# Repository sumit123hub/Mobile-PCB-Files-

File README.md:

# Custom ESP32 Mobile System PCB

I always dreamed of building my own mobile system. This repo documents my custom ESP32 PCB design featuring a GSM module, display interface, and a complete Battery Management System (BMS).

All subsystems were designed in KiCad and independently validated. Schematics, layout, and testing are complete—I'm just sourcing a suitable display for final integration.

---

## 📷 PCB Images

| Front | Back | 
| :---: | :---: |
|  |  | 

---

| KiCad View |
| :---: |
|  |

---

## ✨ What's on the Board

| Component | Description |
| :--- | :--- |
| **ESP32-WROOM** | Main microcontroller (WiFi + BLE) |
| **GSM Module** | Quectel M65 module |
| **Charging Circuit** | BQ Chip |
| **Display Interface** | SPI for display and I2C for charhing |

---

## 📂 Files

- `Mobile_System.kicad_sch` – Schematic
- `Mobile_System.kicad_pcb` – PCB layout
- `gerbers/` – Manufacturing files
- `BOM.csv` – Bill of Materials

---

## 📌 Status

- ✅ Schematic – Complete
- ✅ PCB Layout – Complete
- ✅ BMS Validation – Passed
- ✅ GSM Validation – Passed
- ⏳ Display Integration – In progress (sourcing)
- ⏳ Firmware – Next step

---

## 🛠️ Tools

- **KiCad** – PCB design
- **Arduino / PlatformIO** – Firmware (coming soon)

---

## 👤 Author

**Sumit Sigdel**  
GitHub: [sumit123hub](https://github.com/sumit123hub)

---

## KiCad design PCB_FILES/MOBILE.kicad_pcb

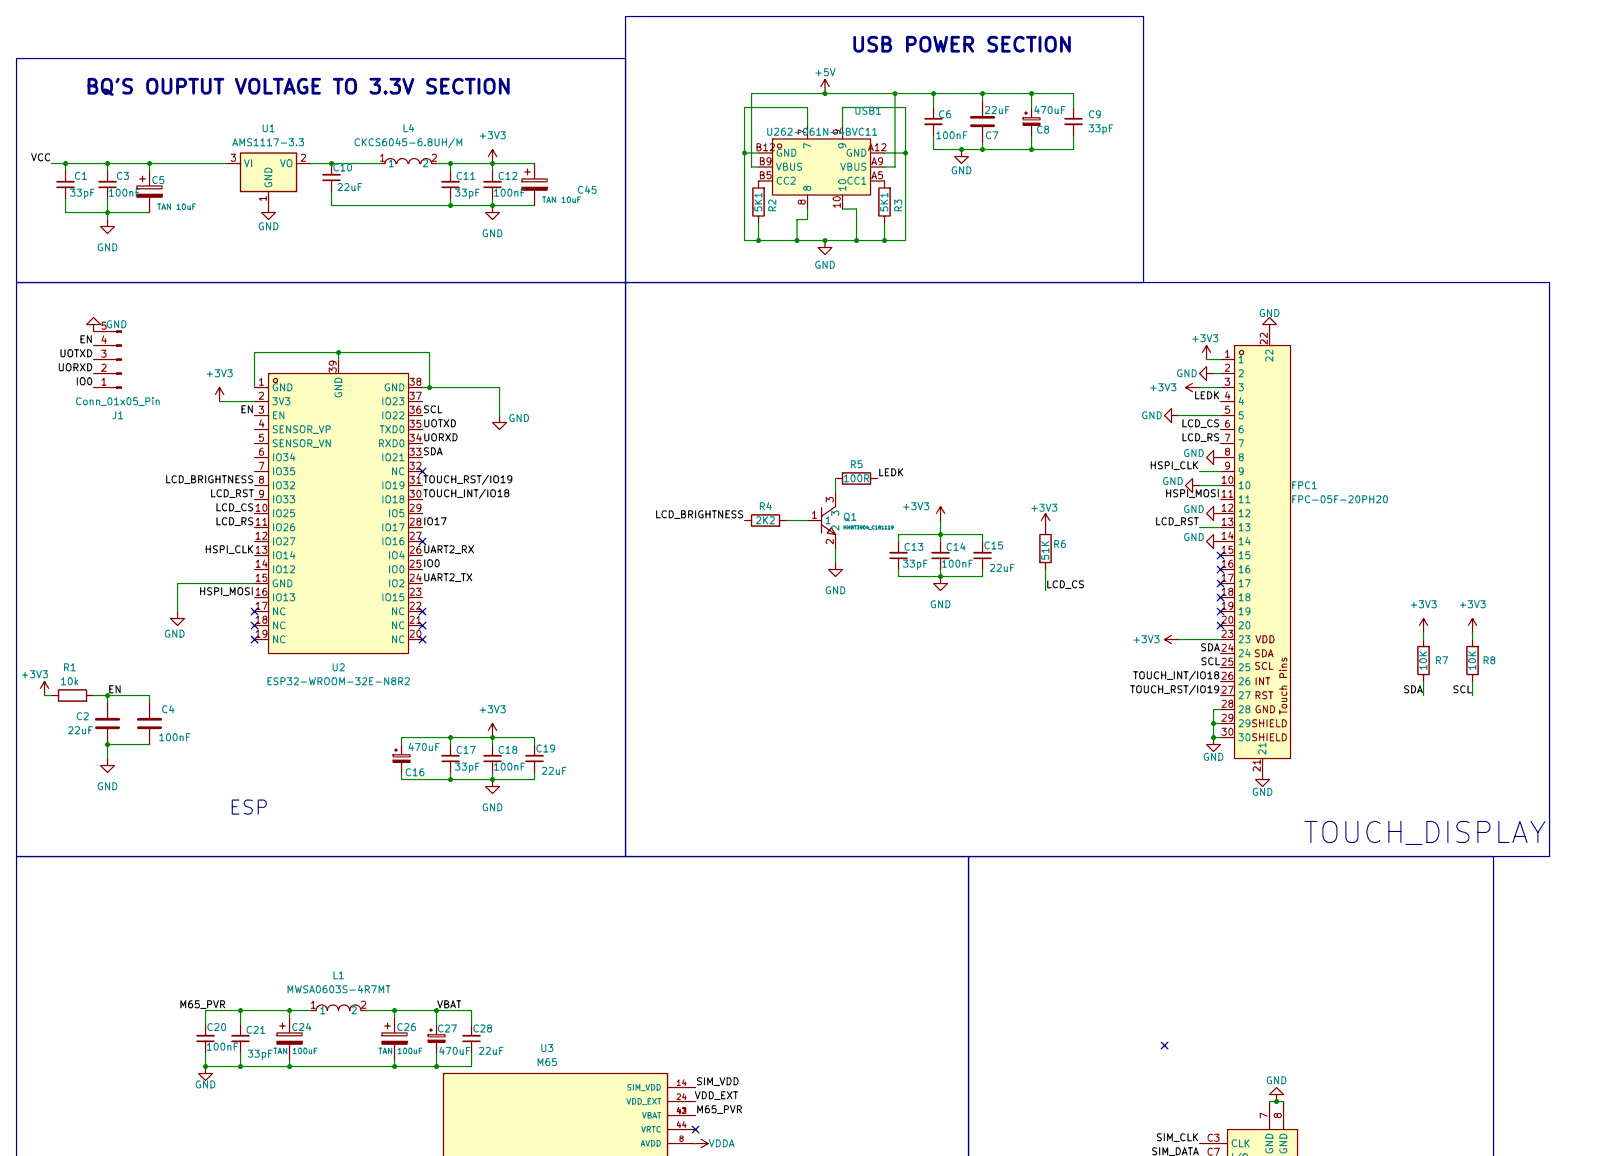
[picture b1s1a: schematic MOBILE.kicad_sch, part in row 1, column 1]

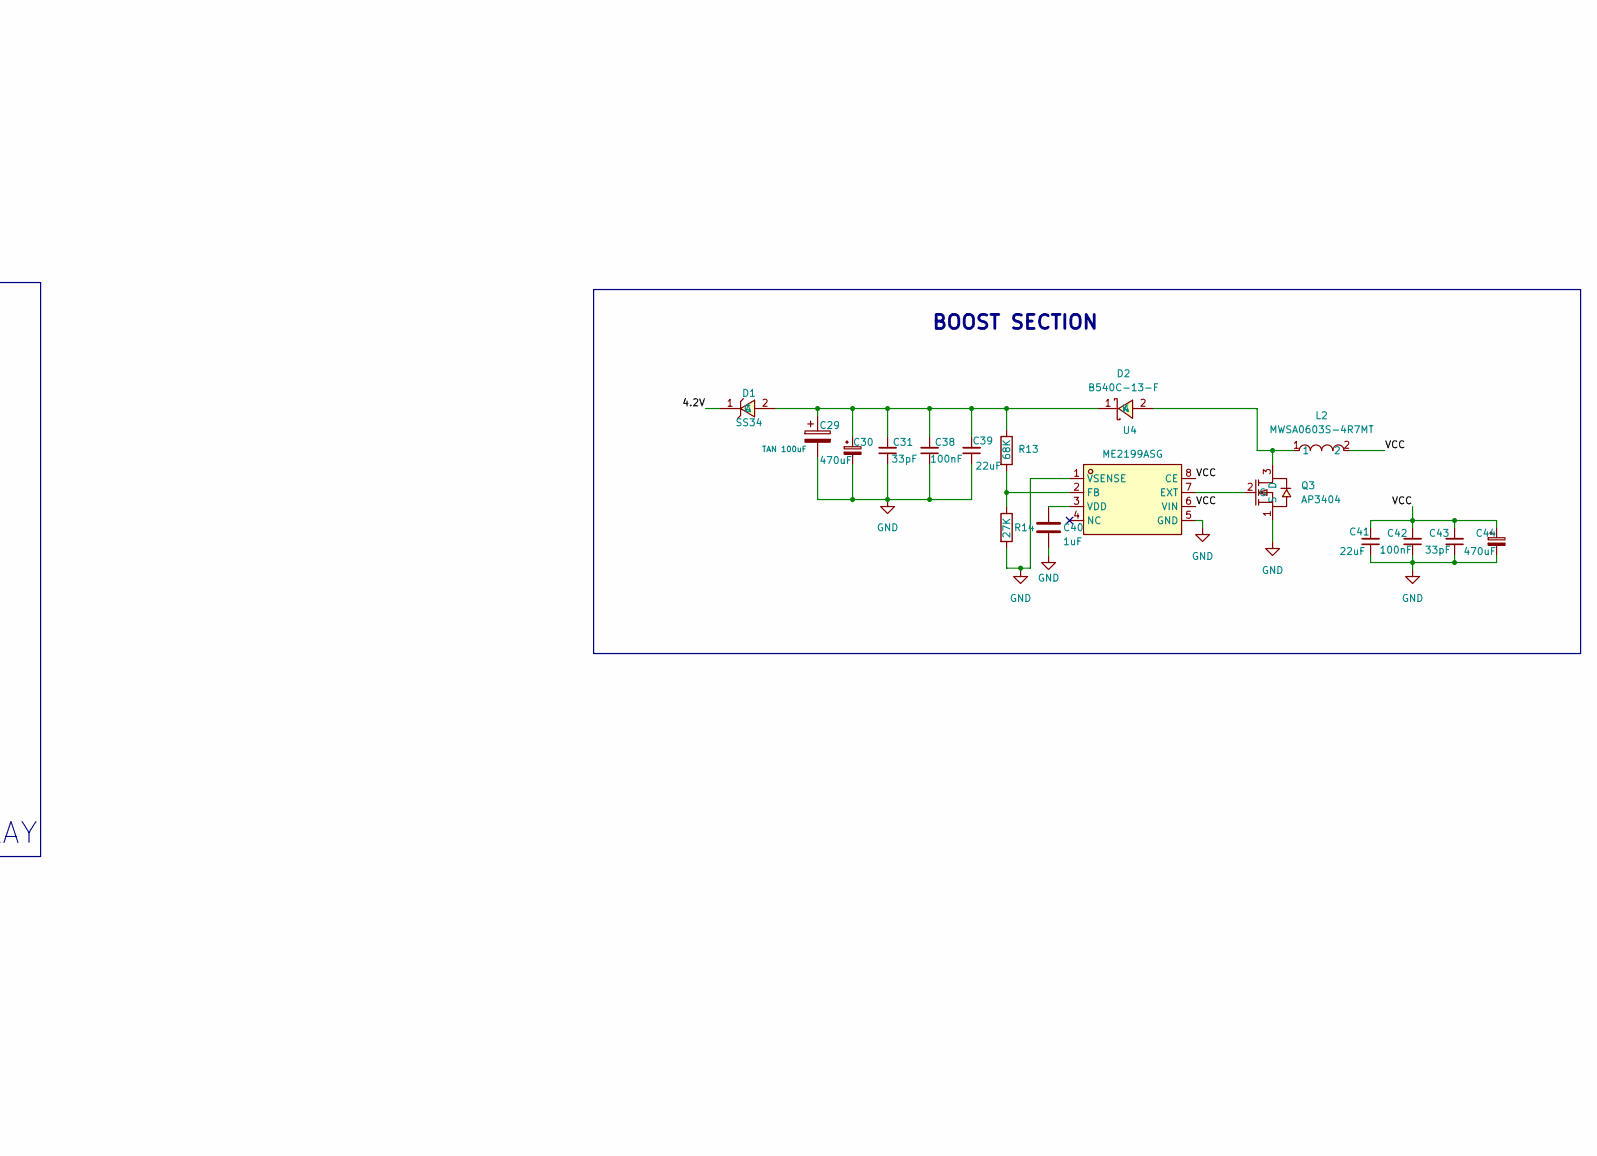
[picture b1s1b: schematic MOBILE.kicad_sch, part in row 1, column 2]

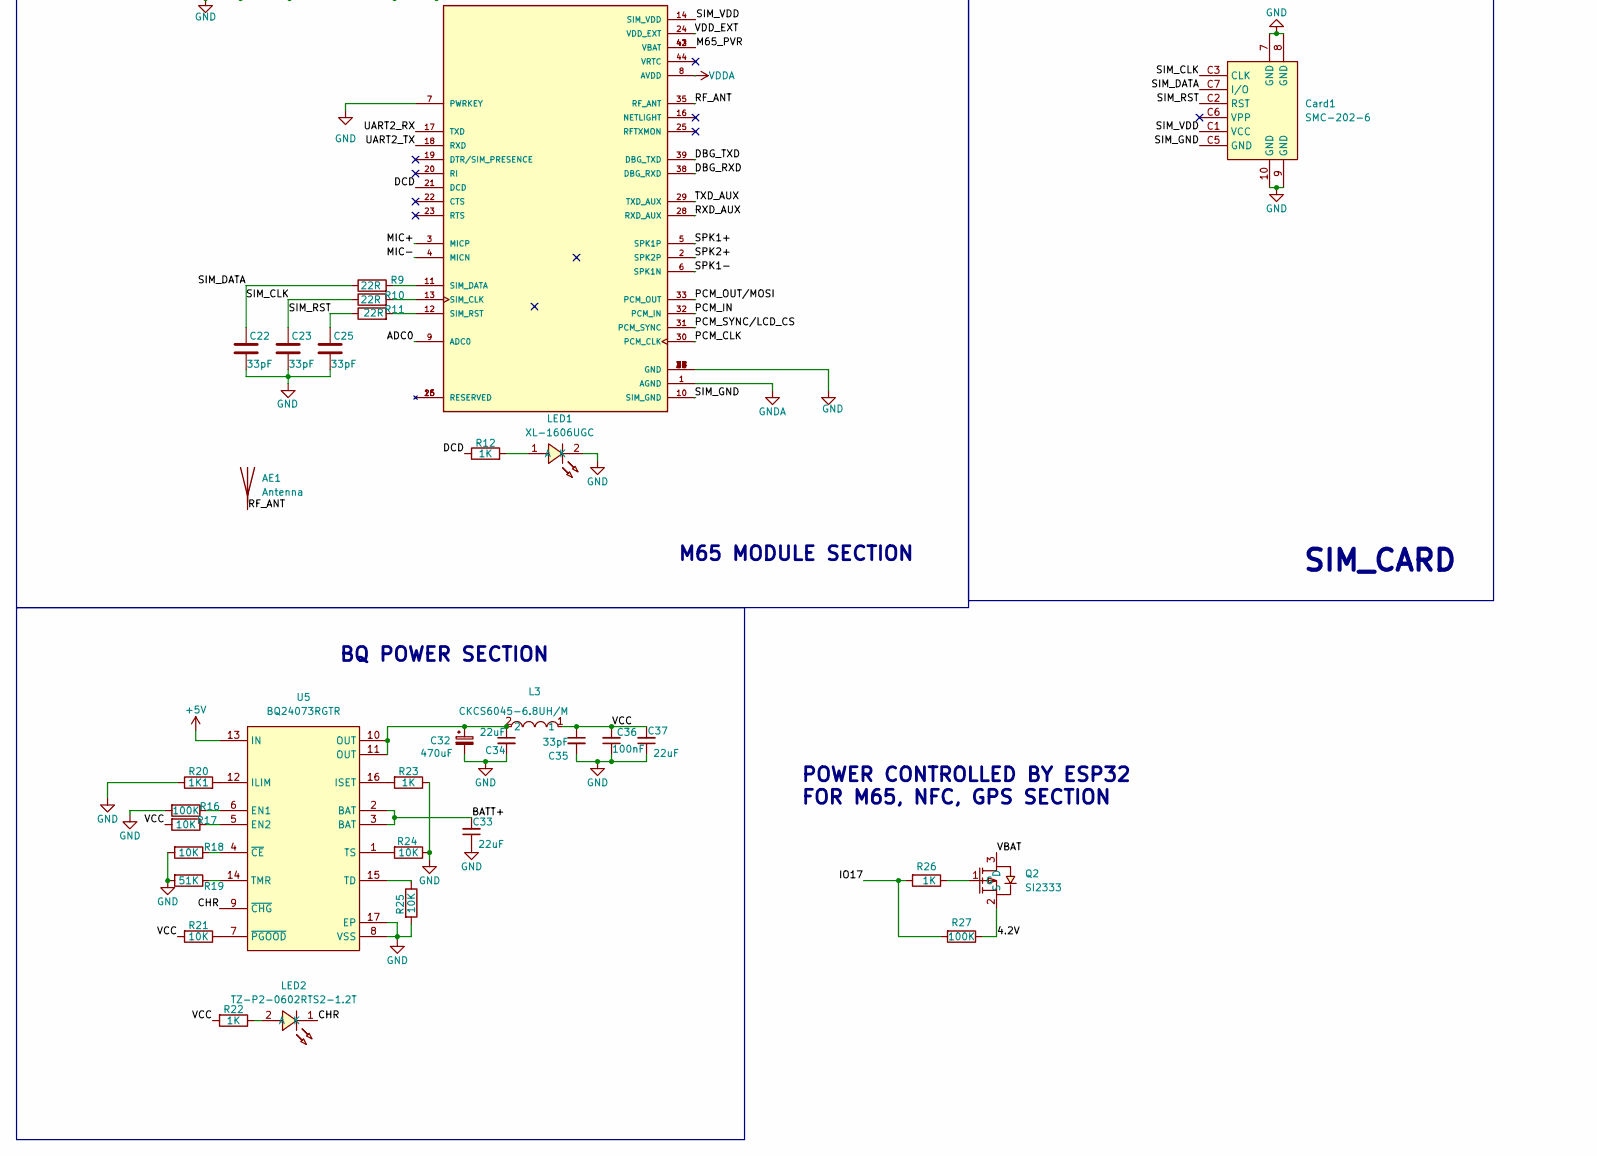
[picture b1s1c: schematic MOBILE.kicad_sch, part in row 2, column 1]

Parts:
AE1: Antenna; Texas_SWRA416_868MHz_915MHz
C1, C11, C13, C17, C21, C31, C35, C43: 33pF; C_0805_2012Metric; LCSC Part # C696910
C2: 22uF; C_0805_2012Metric
C3, C12, C14, C18, C20, C36, C38, C42: 100nF; C_0805_2012Metric; LCSC Part # C392963
C4: 100nF; C_0805_2012Metric
C5, C45: TAN 10uF; CP_EIA-3216-18_Kemet-A; LCSC Part # C27279
C6: 100nF; C_0805_2012Metric; LCSC Part C392963
C7, C10, C15, C19, C28, C33, C34, C37, C39, C41: 22uF; C_0805_2012Metric; LCSC Part # C5674
C8, C16, C27, C30, C32, C44: 470uF; CP_Elec_6.3x7.7; LCSC Part # C5189822
C9, C22, C23, C25: 33pF; C_0805_2012Metric; LCSC Part C696910
C24, C26, C29: TAN 100uF; CP_EIA-3216-18_Kemet-A; LCSC Part # C27279
C40: 1uF; C_0805_2012Metric; LCSC Part C28323
Card1: SMC-202-6; SIM-SMD_SMC-202-6; LCSC Part C266634
D1: SS34; DO-214AC_L4.3-W2.7-LS5.0-RD; LCSC Part # C2836396
D2: B540C-13-F; SMC_L7.1-W6.2-LS8.1-RD; LCSC Part C72264
FPC1: FPC-05F-20PH20; touch_display_3.5inch; LCSC Part C2856803
J1: Conn_01x05_Pin; PinHeader_1x05_P2.54mm_Vertical
L1, L2: MWSA0603S-4R7MT; IND-SMD_L7.0-W6.6; LCSC Part C408447
L3, L4: CKCS6045-6.8UH/M; IND-SMD_L6.0-W6.0; LCSC Part C57254
LED1: XL-1606UGC; LED-SMD_L1.7-W1.1-R-RD_GREEN; LCSC Part C965863
LED2: TZ-P2-0602RTS2-1.2T; LED-SMD_L1.6-W1.2-RD; LCSC Part C688879
Q1: MMBT3904_C181119; SOT-23-3_L2.9-W1.6-P1.90-LS2.8-BR; LCSC Part C181119
Q2: SI2333; SOT-23_L2.9-W1.3-P1.90-LS2.4-BR; LCSC Part C4748717
Q3: AP3404; SOT-23-3_L2.9-W1.3-P1.90-LS2.4-BR-2; LCSC Part C2842665
R1: 10k; R_0603_1608Metric
R2, R3: 5K1; R_0603_1608Metric; LCSC Part # C2907114
R4: 2K2; R_0603_1608Metric; LCSC Part C2907117
R5: 100R; R_0603_1608Metric; LCSC Part C125923
R6: 51K; R_0603_1608Metric; LCSC Part C2907180
R7, R8, R17, R18, R21, R24, R25: 10K; R_0603_1608Metric; LCSC Part # C3017715
R9, R10, R11: 22R; R_0603_1608Metric; LCSC Part C3016215
R12: 1K; R_0603_1608Metric; LCSC Part # C2907179
R13: 68K; R_0603_1608Metric; LCSC Part C2907196
R14: 27K; R_0603_1608Metric; LCSC Part C22967
R16, R27: 100K; R_0603_1608Metric; LCSC Part # C25803
R19: 51K; R_0603_1608Metric; LCSC Part # C2907180
R20: 1K1; R_0603_1608Metric; LCSC Part # C2906975
R22: 1K; R_0603_1608Metric; LCSC Part # C103309
R23, R26: 1K; R_0603_1608Metric; LCSC Part # C3017736
U1: AMS1117-3.3; SOT-223-3_TabPin2
U2: ESP32-WROOM-32E-N8R2; WIFI-SMD_ESP32-WROOM-32E; LCSC Part C5361945
U3: M65; XCVR_M65; PARTREV 1.0; LCSC Part Y100443
U4: ME2199ASG; SOP-8_L4.9-W3.9-P1.27-LS6.0-BL; LCSC Part # C2875120
U5: BQ24073RGTR; QFN-16_L3.0-W3.0-P0.50-TL-EP1.7; LCSC Part C15220
USB1: U262-061N-4BVC11; USB-SMD_U262-061N-4BVC11; LCSC Part C2764612

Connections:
+3V3: C11.2, C12.2, C13.2, C14.2, C15.2, C16.1, C17.2, C18.2, C19.2, C45.1, FPC1.1, FPC1.3, FPC1.23, L4.2, R1.1, R6.1, R7.2, R8.2, U2.2 (3V3)
+5V: C6.1, C7.1, C8.1, C9.1, U5.13 (IN), USB1.A9 (VBUS), USB1.B9 (VBUS)
/4.2V: D1.1 (C), Q2.2 (S), R27.1
/ADC0: U3.9 (ADC0)
/BATT+: C33.2, U5.2 (BAT), U5.3 (BAT)
/CHR: LED2.1 (K), U5.9 (~CHG)
/DBG_RXD: U3.38 (DBG_RXD)
/DBG_TXD: U3.39 (DBG_TXD)
/DCD: R12.1, U3.21 (DCD)
/EN: C2.1, C4.1, J1.4, R1.2, U2.3 (EN)
/HSPI_CLK: FPC1.9, U2.13 (IO14)
/HSPI_MOSI: FPC1.11, U2.16 (IO13)
/IO0: J1.1, U2.25 (IO0)
/IO17: R26.2, R27.2, U2.28 (IO17)
/LCD_BRIGHTNESS: R4.1, U2.8 (IO32)
/LCD_CS: FPC1.6, R6.2, U2.10 (IO25)
/LCD_RS: FPC1.7, U2.11 (IO26)
/LCD_RST: FPC1.13, U2.9 (IO33)
/LEDK: FPC1.4, R5.1
/M65_PVR: C20.2, C21.2, C24.1, L1.1, U3.42 (VBAT), U3.43 (VBAT)
/MIC+: U3.3 (MICP)
/MIC-: U3.4 (MICN)
/PCM_CLK: U3.30 (PCM_CLK)
/PCM_IN: U3.32 (PCM_IN)
/PCM_OUT/MOSI: U3.33 (PCM_OUT)
/PCM_SYNC/LCD_CS: U3.31 (PCM_SYNC)
/RF_ANT: AE1.1 (A), U3.35 (RF_ANT)
/RXD_AUX: U3.28 (RXD_AUX)
/SCL: FPC1.25, R8.1, U2.36 (IO22)
/SDA: FPC1.24, R7.1, U2.33 (IO21)
/SIM_CLK: C23.1, Card1.C3 (CLK), R10.1
/SIM_DATA: C22.1, Card1.C7 (I/O), R9.1
/SIM_GND: Card1.C5 (GND), U3.10 (SIM_GND)
/SIM_RST: C25.1, Card1.C2 (RST), R11.1
/SIM_VDD: Card1.C1 (VCC), U3.14 (SIM_VDD)
/SPK1+: U3.5 (SPK1P)
/SPK1-: U3.6 (SPK1N)
/SPK2+: U3.2 (SPK2P)
/TOUCH_INT/IO18: FPC1.26, U2.30 (IO18)
/TOUCH_RST/IO19: FPC1.27, U2.31 (IO19)
/TXD_AUX: U3.29 (TXD_AUX)
/UART2_RX: U2.26 (IO4), U3.17 (TXD)
/UART2_TX: U2.24 (IO2), U3.18 (RXD)
/UORXD: J1.2, U2.34 (RXD0)
/UOTXD: J1.3, U2.35 (TXD0)
/VBAT: C26.1, C27.1, C28.2, L1.2, Q2.3 (D)
/VCC: C1.2, C3.2, C5.1, C35.1, C36.2, C37.2, C41.2, C42.2, C43.2, C44.1, L2.2, L3.1, R17.2, R21.2, R22.2, U1.3 (VI), U4.6 (VIN), U4.8 (CE)
/VDD_EXT: U3.24 (VDD_EXT)
GND: C1.1, C2.2, C3.1, C4.2, C5.2, C6.2, C7.2, C8.2, C9.2, C10.1, C11.1, C12.1, C13.1, C14.1, C15.1, C16.2, C17.1, C18.1, C19.1, C20.1, C21.1, C22.2, C23.2, C24.2, C25.2, C26.2, C27.2, C28.1, C29.2, C30.2, C31.1, C32.2, C33.1, C34.2, C35.2, C36.1, C37.1, C38.1, C39.1, C40.1, C41.1, C42.1, C43.1, C44.2, C45.2, Card1.7 (GND), Card1.8 (GND), Card1.9 (GND), Card1.10 (GND), FPC1.2, FPC1.5, FPC1.8, FPC1.10, FPC1.12, FPC1.14, FPC1.21, FPC1.22, FPC1.28, FPC1.29, FPC1.30, J1.5, LED1.2 (K), Q1.2, Q3.1 (S), R2.1, R3.1, R14.2, R16.2, R18.2, R19.2, R20.1, R23.1, R24.1, R25.2, U1.1 (GND), U2.1 (GND), U2.15 (GND), U2.38 (GND), U2.39 (GND), U3.7 (PWRKEY), U3.27 (GND), U3.34 (GND), U3.36 (GND), U3.37 (GND), U3.40 (GND), U3.41 (GND), U4.1 (VSENSE), U4.5 (GND), U5.8 (VSS), U5.17 (EP), USB1.7, USB1.8, USB1.9, USB1.10, USB1.A12 (GND), USB1.B12 (GND)
GNDA: U3.1 (AGND)
unnamed: C32.1, C34.1, L3.2, U5.10 (OUT), U5.11 (OUT)
unnamed: C29.1, C30.1, C31.2, C38.2, C39.2, D1.2 (A), D2.1 (K), R13.1
unnamed: D2.2 (A), L2.1, Q3.3 (D)
unnamed: LED1.1 (A), R12.2
unnamed: LED2.2 (A), R22.1
unnamed: Q1.1, R4.2
unnamed: Q1.3, R5.2
unnamed: Q2.1 (G), R26.1
unnamed: Q3.2 (G), U4.7 (EXT)
unnamed: C10.2, L4.1, U1.2 (VO)
unnamed: R10.2, U3.13 (SIM_CLK)
unnamed: R9.2, U3.11 (SIM_DATA)
unnamed: R11.2, U3.12 (SIM_RST)
unnamed: R13.2, R14.1, U4.2 (FB)
unnamed: C40.2, U4.3 (VDD)
unnamed: R16.1, U5.6 (EN1)
unnamed: R17.1, U5.5 (EN2)
unnamed: R20.2, U5.12 (ILIM)
unnamed: R23.2, U5.16 (ISET)
unnamed: R25.1, U5.15 (TD)
unnamed: R19.1, U5.14 (TMR)
unnamed: R24.2, U5.1 (TS)
unnamed: R18.1, U5.4 (~CE)
unnamed: R21.1, U5.7 (~PGOOD)
unnamed: R3.2, USB1.A5 (CC1)
unnamed: R2.2, USB1.B5 (CC2)
VDDA: U3.8 (AVDD)

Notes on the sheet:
USB POWER SECTION
POWER CONTROLLED BY ESP32 FOR M65, NFC, GPS SECTION
TOUCH_DISPLAY
ESP
SIM_CARD
M65 MODULE SECTION
BOOST SECTION
BQ'S OUPTUT VOLTAGE TO 3.3V SECTION
BQ POWER SECTION

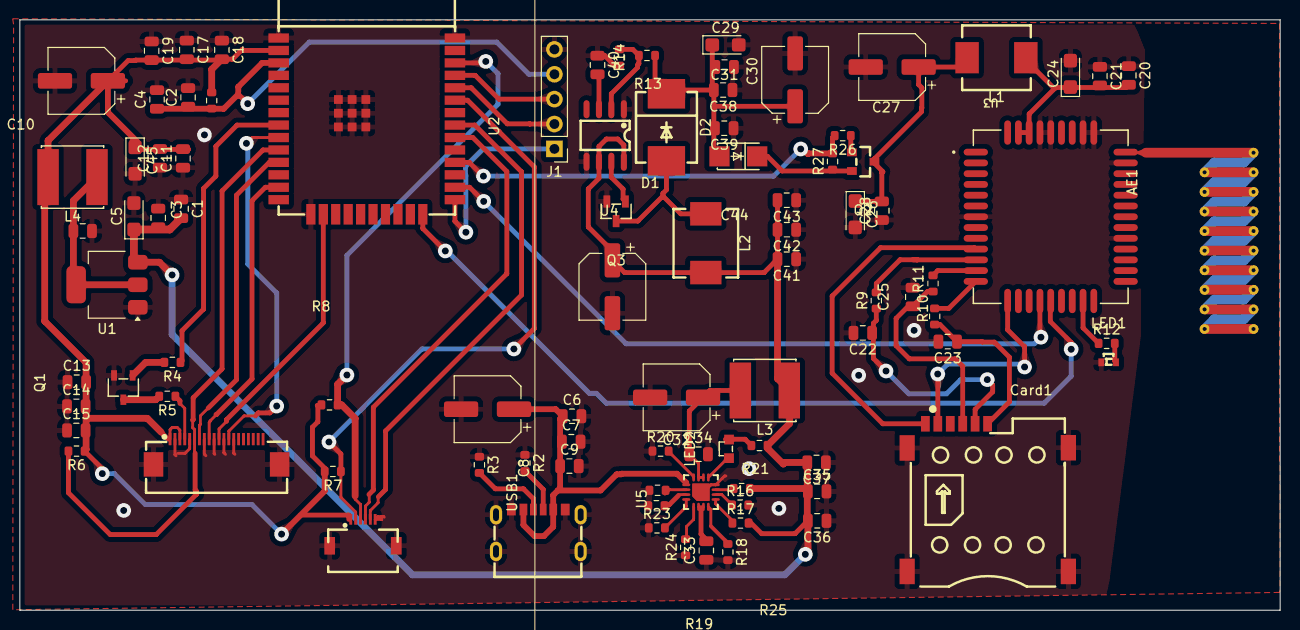
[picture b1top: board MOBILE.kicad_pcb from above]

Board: 2 copper layers, 128.7 x 60.3 mm, 92 parts (0 on the bottom side), 60 nets.

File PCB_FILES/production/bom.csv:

Designator,Footprint,Quantity,Value,LCSC Part #
AE1,Texas_SWRA416_868MHz_915MHz,1,Antenna,
"C1, C11, C13, C17, C21, C22, C23, C25, C31, C35, C43, C9",0805,12,33pF,C696910
"C10, C15, C19, C28, C33, C34, C37, C39, C41, C7",0805,10,22uF,C5674
"C12, C14, C18, C20, C3, C36, C38, C42, C6",0805,9,100nF,C392963
"C16, C27, C30, C32, C44, C8",CP_Elec_6.3x7.7,6,470uF,C5189822 
C2,0805,1,22uF,
"C24, C26, C29",CP_EIA-3216-18_Kemet-A,3,TAN 100uF,C27279
C4,0805,1,100nF,
C40,0805,1,1uF,C28323
"C45, C5",CP_EIA-3216-18_Kemet-A,2,TAN 10uF,C27279
CARD1,SIM-SMD_SMC-202-6,1,SMC-202-6,C266634
D1,DO-214AC_L4.3-W2.7-LS5.0-RD,1,SS34,C2836396
D2,SMC_L7.1-W6.2-LS8.1-RD,1,B540C-13-F,C72264
FPC1,touch_display_3.5inch,1,FPC-05F-20PH20,
J1,PinHeader_1x05_P2.54mm_Vertical,1,Conn_01x05_Pin,
"L1, L2",IND-SMD_L7.0-W6.6,2,MWSA0603S-4R7MT,C2937097
"L3, L4",IND-SMD_L6.0-W6.0,2,CKCS6045-6.8UH/M,C57254
LED1,LED-SMD_L1.7-W1.1-R-RD_GREEN,1,XL-1606UGC,C965863
LED2,LED-SMD_L1.6-W1.2-RD,1,TZ-P2-0602RTS2-1.2T,C688879
Q1,SOT-23-3_L2.9-W1.6-P1.90-LS2.8-BR,1,MMBT3904_C181119,C181119
Q2,SOT-23_L2.9-W1.3-P1.90-LS2.4-BR,1,SI2333,C4748717
Q3,SOT-23-3_L2.9-W1.3-P1.90-LS2.4-BR-2,1,AP3404,C2842665
R1,0603,1,10k,
"R10, R11, R9",0603,3,22R,C3016215
R12,0603,1,1K,C2907179
R13,0603,1,68K,C2907196
R14,0603,1,27K,C22967
"R16, R27",0603,2,100K,C25803
"R17, R18, R21, R24, R25, R7, R8",0603,7,10K,C3017715
"R19, R6",0603,2,51K,C2907180
"R2, R3",0603,2,5K1,C2907114
R20,0603,1,1K1,C2906975
R22,0603,1,1K,C103309
"R23, R26",0603,2,1K,C3017736
R4,0603,1,2K2,C2907117
R5,0603,1,100R,C125923 
U1,SOT-223-3_TabPin2,1,AMS1117-3.3,
U2,WIFI-SMD_ESP32-WROOM-32E,1,ESP32-WROOM-32E-N8R2,C5361945
U3,XCVR_M65,1,M65,Y100443
U4,SOP-8_L4.9-W3.9-P1.27-LS6.0-BL,1,ME2199ASG,C2875120
U5,QFN-16_L3.0-W3.0-P0.50-TL-EP1.7,1,BQ24073RGTR,C15220
USB1,USB-SMD_U262-061N-4BVC11,1,U262-061N-4BVC11,C2764612
